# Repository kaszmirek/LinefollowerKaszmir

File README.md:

# LinefollowerKaszmir
robot typu line follower

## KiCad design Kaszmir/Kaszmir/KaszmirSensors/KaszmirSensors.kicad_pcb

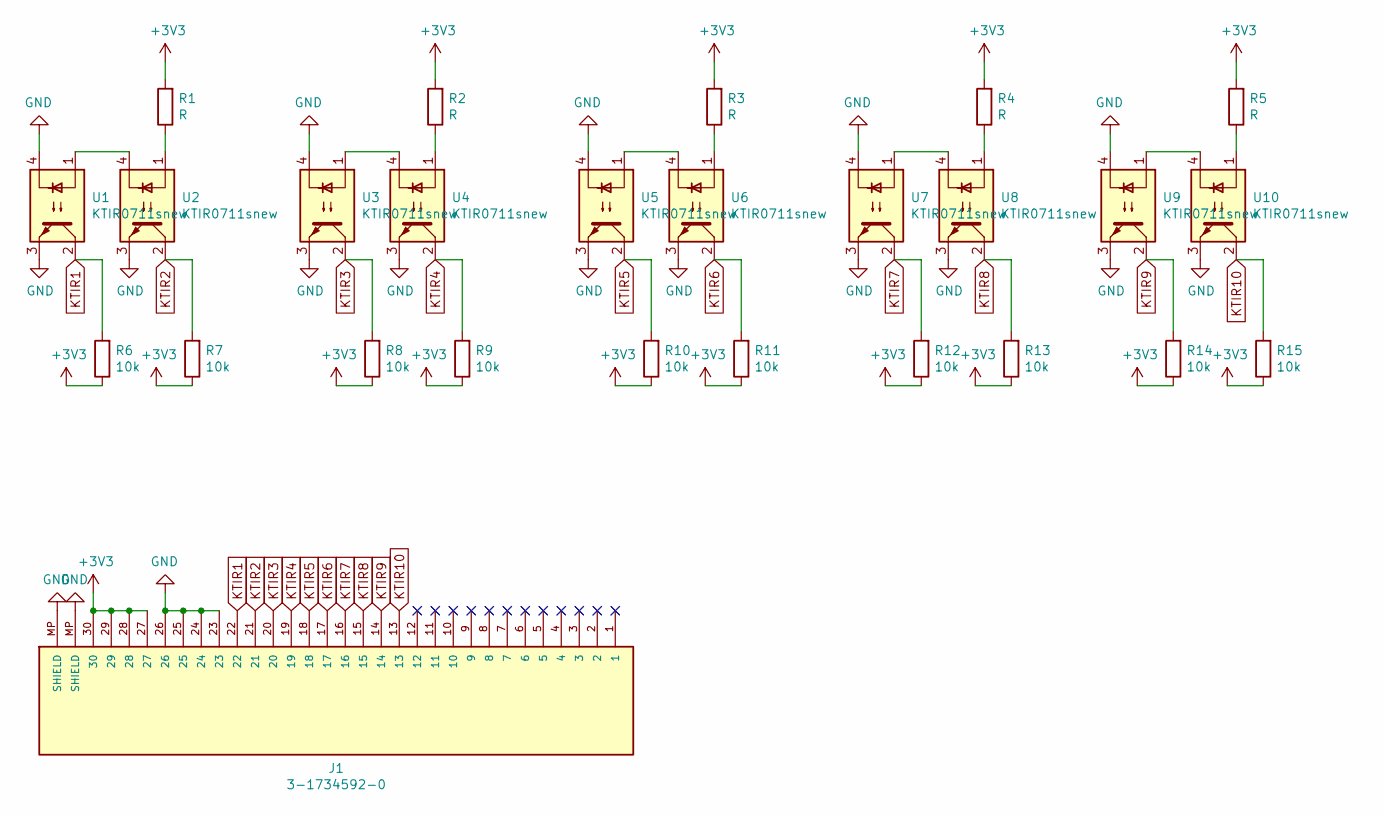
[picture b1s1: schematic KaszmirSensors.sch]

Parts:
J1: 3-1734592-0; TE_3-1734592-0; PARTREV C
R1, R2, R3, R4, R5: R; R_0603_1608Metric
R6, R7, R8, R9, R10, R11, R12, R13, R14, R15: 10k; R_0603_1608Metric
U1, U2, U3, U4, U5, U6, U7, U8, U9, U10: KTIR0711snew; KTIR0711s

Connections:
+3V3: J1.27, J1.28, J1.29, J1.30, R1.2, R2.2, R3.2, R4.2, R5.2, R6.1, R7.1, R8.1, R9.1, R10.1, R11.1, R12.1, R13.1, R14.1, R15.1
GND: J1.23, J1.24, J1.25, J1.26, J1.MP (SHIELD), U1.3, U1.4, U2.3, U3.3, U3.4, U4.3, U5.3, U5.4, U6.3, U7.3, U7.4, U8.3, U9.3, U9.4, U10.3
KTIR1: J1.22, R6.2, U1.2
KTIR2: J1.21, R7.2, U2.2
KTIR3: J1.20, R8.2, U3.2
KTIR4: J1.19, R9.2, U4.2
KTIR5: J1.18, R10.2, U5.2
KTIR6: J1.17, R11.2, U6.2
KTIR7: J1.16, R12.2, U7.2
KTIR8: J1.15, R13.2, U8.2
KTIR9: J1.14, R14.2, U9.2
KTIR10: J1.13, R15.2, U10.2
unnamed: R1.1, U2.1
unnamed: R2.1, U4.1
unnamed: R3.1, U6.1
unnamed: R4.1, U8.1
unnamed: R5.1, U10.1
unnamed: U1.1, U2.4
unnamed: U3.1, U4.4
unnamed: U5.1, U6.4
unnamed: U7.1, U8.4
unnamed: U9.1, U10.4

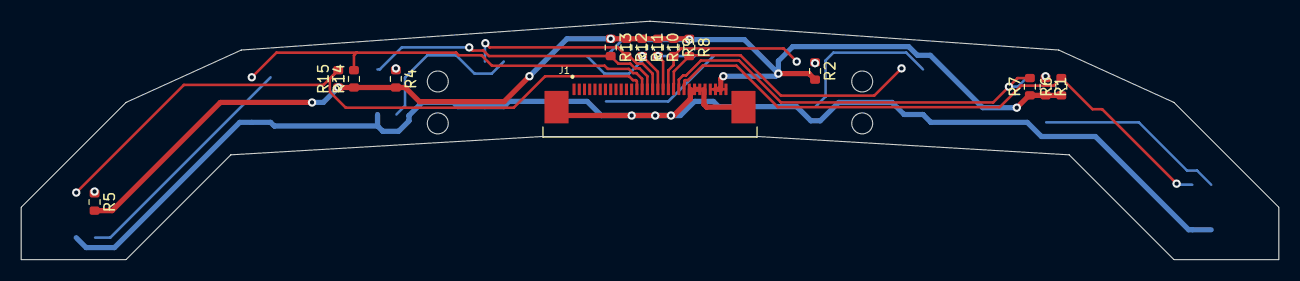
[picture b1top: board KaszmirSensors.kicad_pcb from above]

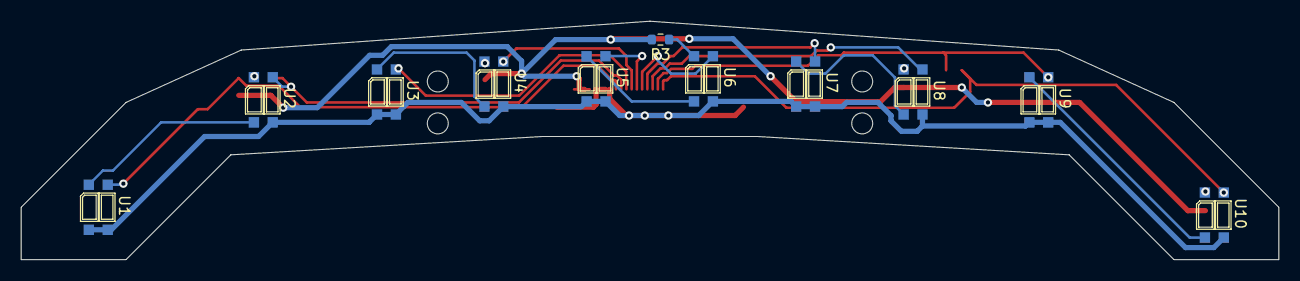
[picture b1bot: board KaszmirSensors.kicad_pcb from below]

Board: 2 copper layers, 120.0 x 22.8 mm, 26 parts (11 on the bottom side), 22 nets.

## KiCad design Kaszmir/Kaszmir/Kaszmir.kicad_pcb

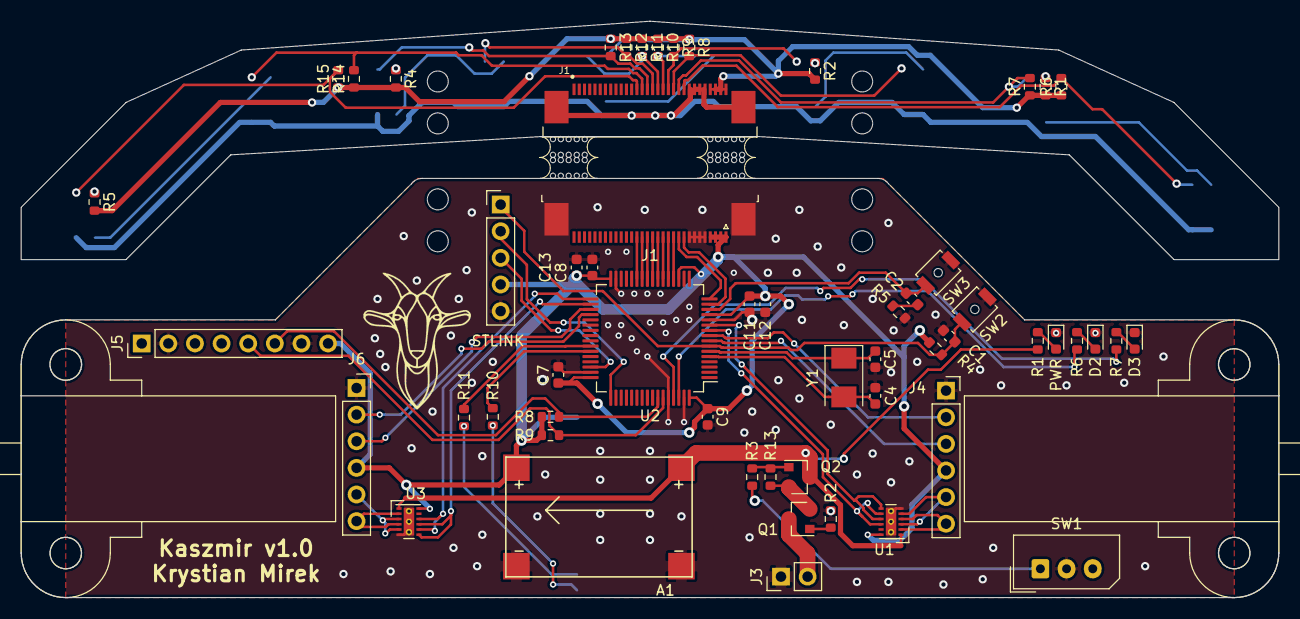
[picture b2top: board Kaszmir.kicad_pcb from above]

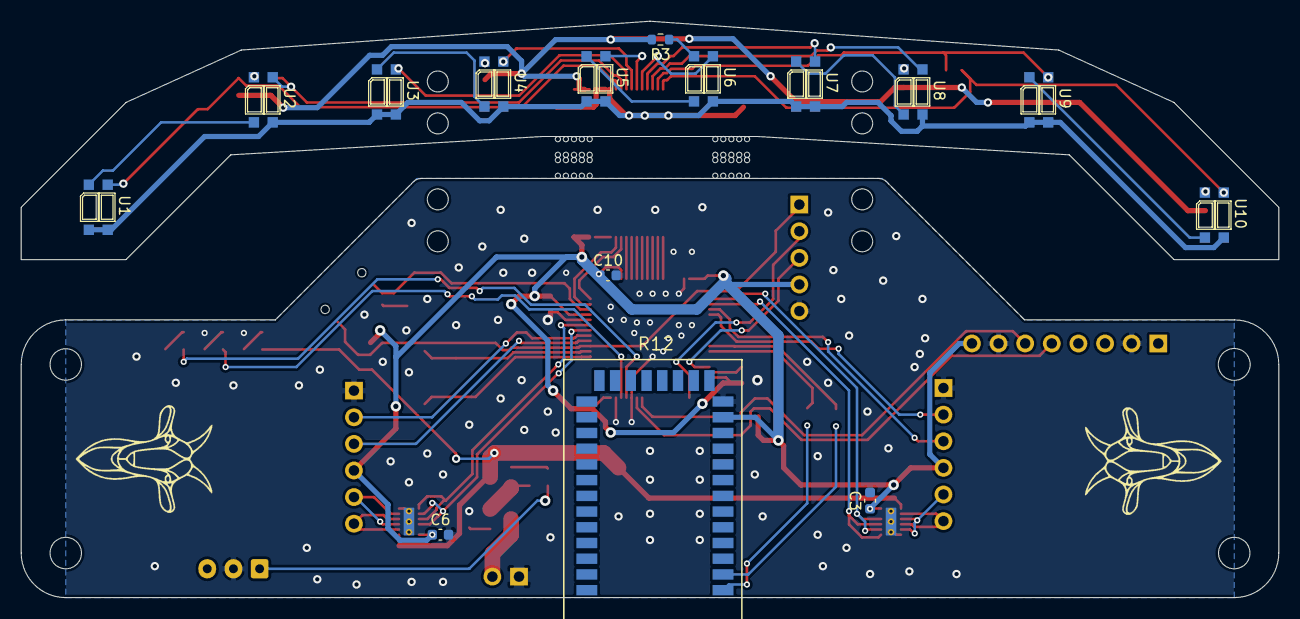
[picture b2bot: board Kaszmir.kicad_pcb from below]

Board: 2 copper layers, 120.0 x 55.0 mm, 75 parts (15 on the bottom side), 48 nets.

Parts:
A1: Mini360_Module
C1, C2, C3, C6, C7, C8, C9, C10: 100n; C_0603_1608Metric
C4, C5: 20p; C_0603_1608Metric
C11: 10n; C_0603_1608Metric
C12: 1u; C_0603_1608Metric
C13: 4.7u; C_0603_1608Metric
D1: PWR; LED_0603_1608Metric
D2, D3: LED; LED_0603_1608Metric
J1: 3-1734592-0; TE_3-1734592-0
J1#2: 3-1734592-0; TE_3-1734839-0_1x30-1MP_P0.5mm_Horizontal
J3: Battery; PinHeader_1x02_P2.54mm_Vertical
J4, J6: Conn_01x06; PinSocket_1x06_P2.54mm_Vertical
J5: Conn_01x08; PinHeader_1x08_P2.54mm_Vertical
Q1, Q2: AO3401A; SOT-23
R1, R2, R3, R4, R5: R; R_0603_1608Metric
R1#2, R2#2, R3#2, R10#2, R11#2: 1k; R_0603_1608Metric
R4#2, R6, R7, R8, R9, R10, R11, R12, R13, R13#2, R14, R15: 10k; R_0603_1608Metric
R5#2: 100; R_0603_1608Metric
R6#2, R7#2: 330; R_0603_1608Metric
R8#2, R9#2: 4,7k; R_0603_1608Metric
R12#2: hm10; HM10
STLINK: Conn_01x05; PinHeader_1x05_P2.54mm_Vertical
SW1: SW_Push_SPDT; Molex_SPOX_5267-03A_1x03_P2.50mm_Vertical
SW2: RST; SW_SPST_B3U-1000P-B
SW3: B1; SW_SPST_B3U-1000P-B
U1, U2, U3, U4, U5, U6, U7, U8, U9, U10: KTIR0711snew; KTIR0711s
U1#2, U3#2: DRV8835; WSON-12-1EP_3x2mm_P0.5mm_EP1x2.65_ThermalVias
U2#2: STM32F103R8Tx; LQFP-64_10x10mm_P0.5mm
Y1: Crystal; Crystal_SMD_5032-2Pin_5.0x3.2mm
mouse-bite-3mm-slot, mouse-bite-3mm-slot#2, mouse-bite-3mm-slot#3, mouse-bite-3mm-slot#4: VAL**; mouse-bite-3mm-slot

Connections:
+3V3: A1.3, C3.1, C6.1, C7.1, C8.1, C9.1, C10.1, C11.1, C12.1, C13.1, J1#2.1, J1#2.2, J1#2.3, J1#2.4, J4.4, J5.8, J6.4, R4#2.1, R8#2.2, R9#2.2, R12#2.12, STLINK.4, U1#2.12, U2#2.13, U2#2.19, U2#2.32, U2#2.48, U2#2.64, U3#2.12
GND: A1.2, A1.4, C1.2, C3.2, C4.2, C5.2, C6.2, C7.2, C8.2, C9.2, C10.2, C11.2, C12.2, C13.2, D1.1, D2.1, D3.1, J1#2.5, J1#2.6, J1#2.7, J1#2.8, J1#2.MP, J3.1, J4.1, J5.2, J5.7, J6.1, R2#2.2, R5#2.2, R12#2.13, STLINK.5, SW1.2, SW2.1, SW3.1, U1#2.6, U1#2.13, U2#2.12, U2#2.18, U2#2.31, U2#2.47, U2#2.60, U2#2.63, U3#2.6, U3#2.13
KTIR1: J1#2.9, U2#2.15
KTIR2: J1#2.10, U2#2.16
KTIR3: J1#2.11, U2#2.20
KTIR4: J1#2.12, U2#2.21
KTIR5: J1#2.13, U2#2.22
KTIR6: J1#2.14, U2#2.23
KTIR7: J1#2.15, U2#2.24
KTIR8: J1#2.16, U2#2.25
KTIR9: J1#2.17, U2#2.26
KTIR10: J1#2.18, U2#2.27
M1_A: J4.3, U2#2.8
M1_B: J4.2, U2#2.9
M1_L: U1#2.8, U1#2.10, U2#2.10
M1_R: U1#2.7, U1#2.9, U2#2.11
M2_A: J6.3, U2#2.35
M2_B: J6.2, U2#2.36
M2_L: U2#2.33, U3#2.8, U3#2.10
M2_R: U2#2.34, U3#2.7, U3#2.9
unnamed: C2.1, SW3.2, U2#2.14
unnamed: C2.2, R5#2.1
unnamed: C4.1, U2#2.5, Y1.2
unnamed: C5.1, U2#2.6, Y1.1
unnamed: D1.2, R1#2.2
unnamed: D2.2, R6#2.2
unnamed: D3.2, R7#2.2
unnamed: J3.2, Q1.3
unnamed: J4.5, U1#2.3, U1#2.5
unnamed: J4.6, U1#2.2, U1#2.4
unnamed: J6.5, U3#2.3, U3#2.5
unnamed: J6.6, U3#2.2, U3#2.4
unnamed: Q1.1, R2#2.1
unnamed: Q1.2, Q2.2, R13#2.1
unnamed: Q2.1, R3#2.1, R13#2.2
unnamed: R3#2.2, SW1.1
unnamed: R6#2.1, U2#2.62
unnamed: R7#2.1, U2#2.61
unnamed: R10#2.2, R12#2.1
unnamed: R11#2.2, R12#2.2
RST: C1.1, R4#2.2, STLINK.1, SW2.2, U2#2.7
RX: R10#2.1, U2#2.43
SCL: J5.6, R8#2.1, U2#2.58
SDA: J5.5, R9#2.1, U2#2.59
SWCLK: STLINK.2, U2#2.49
SWDIO: STLINK.3, U2#2.46
TX: R11#2.1, U2#2.42
VCC: A1.1, Q2.3, R1#2.1, U1#2.1, U3#2.1

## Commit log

2021-05-30 dodanie wszytkiego
2021-05-30 dokumentacja
